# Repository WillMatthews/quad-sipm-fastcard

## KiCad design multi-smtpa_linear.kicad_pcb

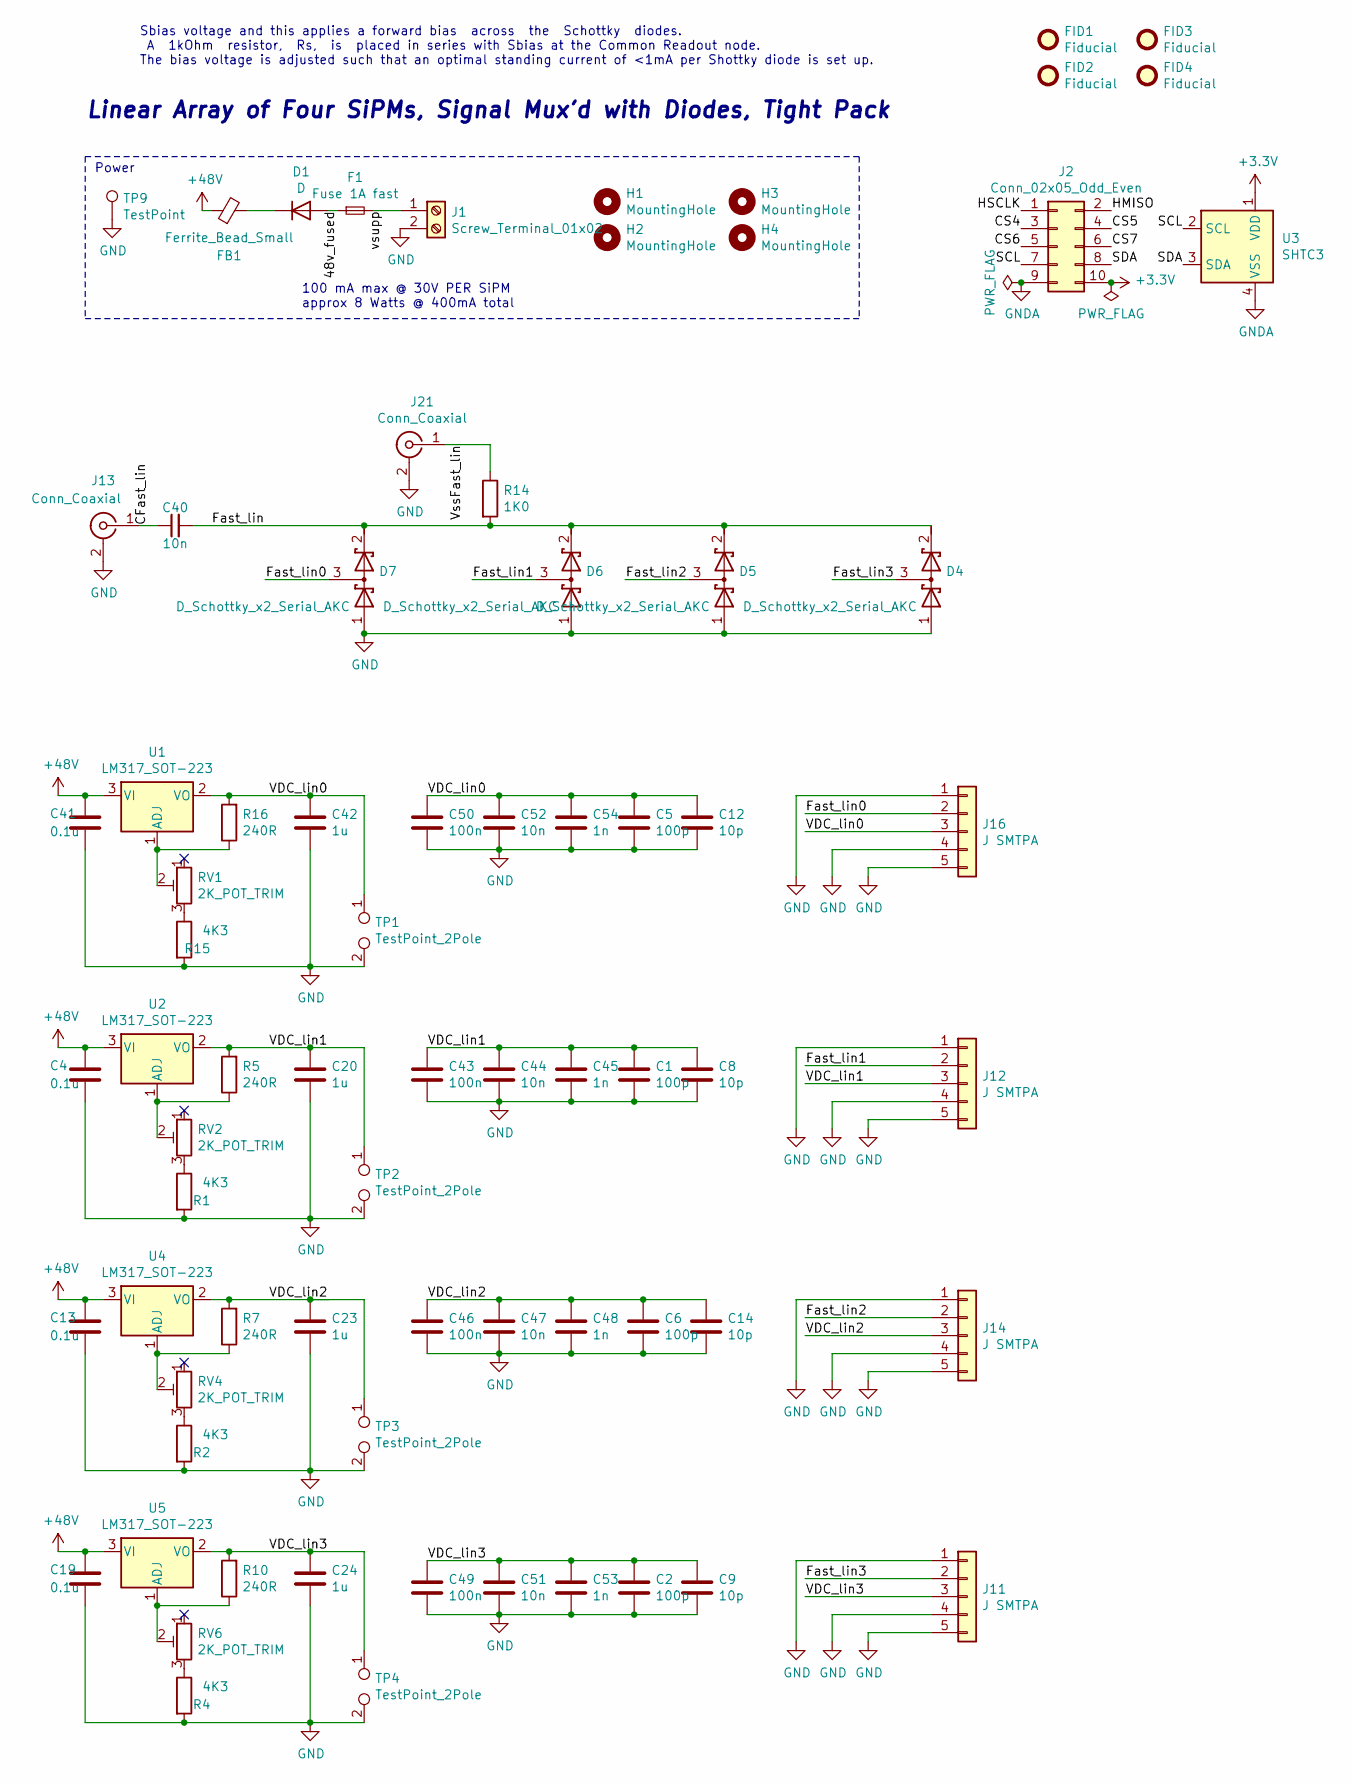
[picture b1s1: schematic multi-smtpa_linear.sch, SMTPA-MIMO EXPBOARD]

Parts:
C1, C2, C5, C6: 100p; C_0402_1005Metric
C4, C13, C19, C41: 0.1u; C_0805_2012Metric_Pad1.15x1.40mm_HandSolder
C8, C9, C12, C14: 10p; C_0402_1005Metric
C20, C23, C24, C42: 1u; C_0805_2012Metric_Pad1.15x1.40mm_HandSolder
C40, C44, C47, C51, C52: 10n; C_0603_1608Metric_Pad1.05x0.95mm_HandSolder
C43, C46, C49, C50: 100n; C_0603_1608Metric_Pad1.05x0.95mm_HandSolder
C45, C48, C53, C54: 1n; C_0603_1608Metric_Pad1.05x0.95mm_HandSolder
D1: D; D_A-405_P10.16mm_Horizontal
D4, D5, D6, D7: D_Schottky_x2_Serial_AKC; SOT-23; Part SMS7621-005LF SOT23
F1: Fuse 1A fast; R_Axial_DIN0207_L6.3mm_D2.5mm_P10.16mm_Horizontal
FB1: Ferrite_Bead_Small; L_0603_1608Metric_Pad1.05x0.95mm_HandSolder
FID1, FID2, FID3, FID4: Fiducial; Fiducial_1mm_Mask3mm
H1, H2, H3, H4: MountingHole; MountingHole_4.3mm_M4_Pad_Via
J1: Screw_Terminal_01x02; TerminalBlock_TE_282834-2_1x02_P2.54mm_Horizontal
J2: Conn_02x05_Odd_Even; PinSocket_2x05_P2.54mm_Vertical
J11, J12, J14, J16: J SMTPA; SMTPA_J30035
J13, J21: Conn_Coaxial; SMA_Amphenol_132289_EdgeMount
R1, R2, R4, R15: 4K3; R_0805_2012Metric_Pad1.15x1.40mm_HandSolder
R5, R7, R10, R16: 240R; R_0805_2012Metric_Pad1.15x1.40mm_HandSolder
R14: 1K0; R_0603_1608Metric_Pad1.05x0.95mm_HandSolder
RV1, RV2, RV4, RV6: 2K_POT_TRIM; Potentiometer_Bourns_3314G_Vertical; Part 987-1161-ND
TP1, TP2, TP3, TP4: TestPoint_2Pole; TestPoint_2Pads_Pitch5.08mm_Drill1.3mm
TP9: TestPoint; TestPoint_Pad_4.0x4.0mm
U1, U2, U4, U5: LM317_SOT-223; SOT-223-3_TabPin2
U3: SHTC3; AMS_QFN-4-1EP_2x2mm_P0.95mm_EP0.7x1.6mm

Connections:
+3V3: J2.10, U3.1 (VDD)
+48V: C4.1, C13.1, C19.1, C41.1, FB1.1, U1.3 (VI), U2.3 (VI), U4.3 (VI), U5.3 (VI)
/48v_fused: D1.2 (A), F1.1
/CFast_lin: C40.1, J13.1 (In)
/CS4: J2.3
/CS5: J2.4
/CS6: J2.5
/CS7: J2.6
/Fast_lin: C40.2, D4.2 (K), D5.2 (K), D6.2 (K), D7.2 (K), R14.2
/Fast_lin0: D7.3 (common), J16.2
/Fast_lin1: D6.3 (common), J12.2
/Fast_lin2: D5.3 (common), J14.2
/Fast_lin3: D4.3 (common), J11.2
/HMISO: J2.2
/HSCLK: J2.1
/SCL: J2.7, U3.2 (SCL)
/SDA: J2.8, U3.3 (SDA)
/VDC_lin0: C5.1, C12.1, C42.1, C50.1, C52.1, C54.1, J16.3, R16.2, TP1.1, U1.2 (VO)
/VDC_lin1: C1.1, C8.1, C20.1, C43.1, C44.1, C45.1, J12.3, R5.2, TP2.1, U2.2 (VO)
/VDC_lin2: C6.1, C14.1, C23.1, C46.1, C47.1, C48.1, J14.3, R7.2, TP3.1, U4.2 (VO)
/VDC_lin3: C2.1, C9.1, C24.1, C49.1, C51.1, C53.1, J11.3, R10.2, TP4.1, U5.2 (VO)
/VssFast_lin: J21.1 (In), R14.1
/vsupp: F1.2, J1.1
GND: C1.2, C2.2, C4.2, C5.2, C6.2, C8.2, C9.2, C12.2, C13.2, C14.2, C19.2, C20.2, C23.2, C24.2, C41.2, C42.2, C43.2, C44.2, C45.2, C46.2, C47.2, C48.2, C49.2, C50.2, C51.2, C52.2, C53.2, C54.2, D4.1 (A), D5.1 (A), D6.1 (A), D7.1 (A), J1.2, J11.1, J11.4, J11.5, J12.1, J12.4, J12.5, J13.2 (Ext), J14.1, J14.4, J14.5, J16.1, J16.4, J16.5, J21.2 (Ext), R1.2, R2.2, R4.2, R15.2, TP1.2, TP2.2, TP3.2, TP4.2, TP9.1
GNDA: J2.9, U3.4 (VSS)
unnamed: D1.1 (K), FB1.2
unnamed: R1.1, RV2.3
unnamed: R2.1, RV4.3
unnamed: R4.1, RV6.3
unnamed: R5.1, RV2.2, U2.1 (ADJ)
unnamed: R7.1, RV4.2, U4.1 (ADJ)
unnamed: R10.1, RV6.2, U5.1 (ADJ)
unnamed: R15.1, RV1.3
unnamed: R16.1, RV1.2, U1.1 (ADJ)

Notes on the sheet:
Linear Array of Four SiPMs, Signal Mux'd with Diodes, Tight Pack
Sbias voltage and this applies a forward bias across the Schottky diodes. A 1kOhm resistor, Rs, is placed in series with Sbias at the Common Readout node. The bias voltage is adjusted such that an optimal standing current of <1mA per Shottky diode is set up.
100 mA max @ 30V PER SiPM approx 8 Watts @ 400mA total
Power

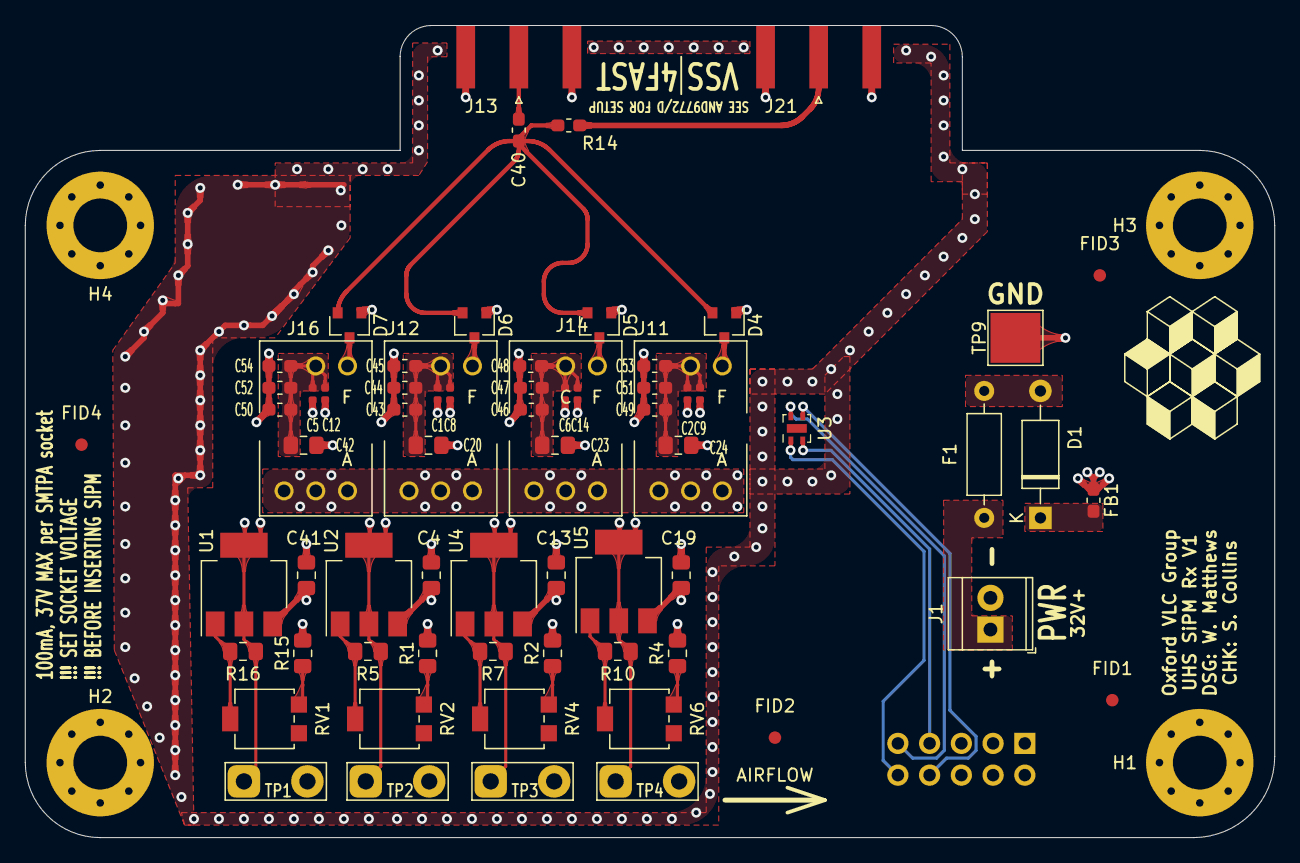
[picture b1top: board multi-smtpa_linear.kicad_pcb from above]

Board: 4 copper layers, 100.0 x 65.0 mm, 75 parts (1 on the bottom side), 28 nets.

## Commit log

2024-04-06 enclosure add
